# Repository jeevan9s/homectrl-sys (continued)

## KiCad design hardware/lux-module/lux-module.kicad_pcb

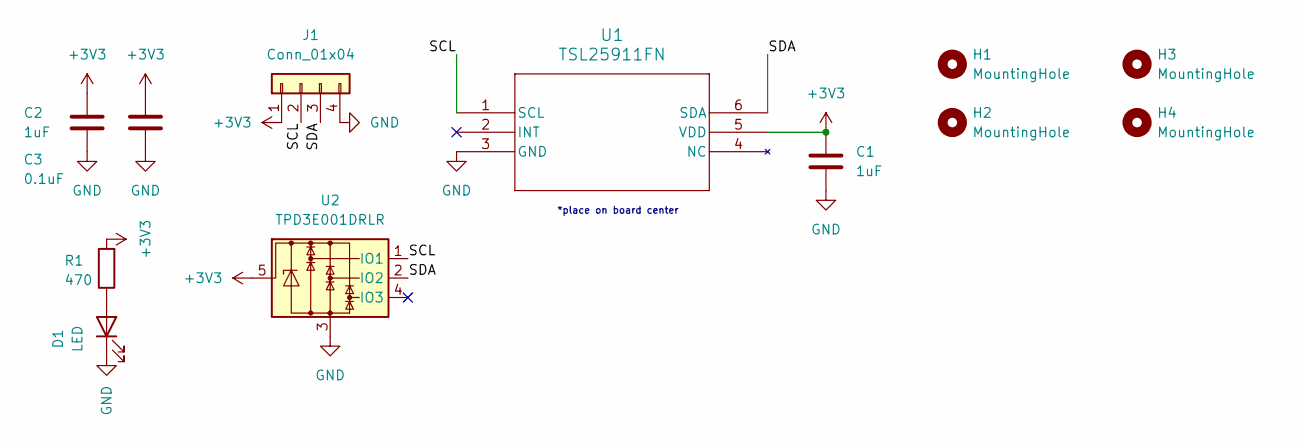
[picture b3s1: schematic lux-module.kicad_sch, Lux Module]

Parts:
C1: 1uF; C_0805_2012Metric; MPN C0805C104K5RACTU
C2: 1uF; C_0805_2012Metric; MPN CL21B106KOQNNNE
C3: 0.1uF; C_0805_2012Metric; MPN CL21B104KBCNNNC
D1: LED; LED_0603_1608Metric
H1, H2, H3, H4: MountingHole; MountingHole_2.2mm_M2; MPN N/A
J1: Conn_01x04; CONN4_S04B-PASK_JST; MPN S04B-PASK-2
R1: 470; R_0402_1005Metric
U1: TSL25911FN; lux-TSL2591; MPN TSL25911FN
U2: TPD3E001DRLR; SOT-553; MPN TPD3E001DRLR

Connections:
+3V3: C1.1, C2.1, C3.1, J1.1, R1.2, U1.5 (VDD), U2.5
/SCL: J1.2, U1.1 (SCL), U2.1 (IO1)
/SDA: J1.3, U1.6 (SDA), U2.2 (IO2)
GND: C1.2, C2.2, C3.2, D1.1 (K), J1.4, U1.3 (GND), U2.3
unnamed: D1.2 (A), R1.1

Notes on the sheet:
*place on board center

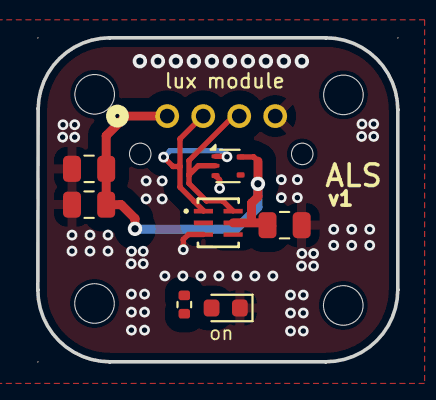
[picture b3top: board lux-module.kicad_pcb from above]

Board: 2 copper layers, 20.0 x 18.0 mm, 12 parts (1 on the bottom side), 5 nets.

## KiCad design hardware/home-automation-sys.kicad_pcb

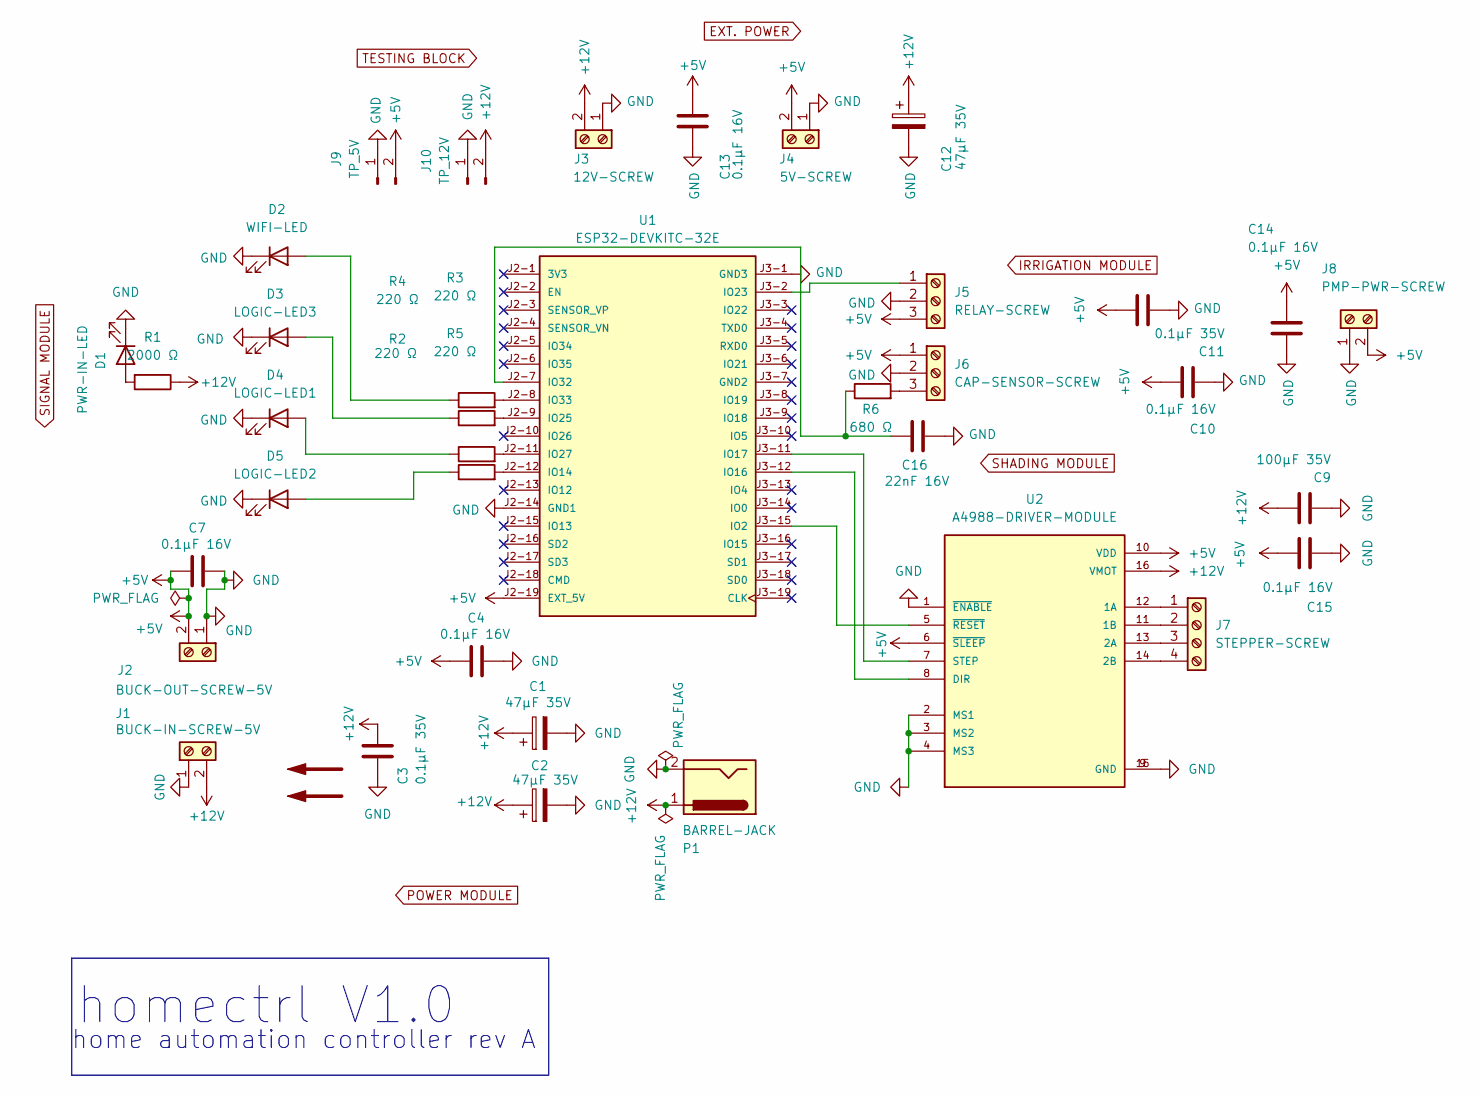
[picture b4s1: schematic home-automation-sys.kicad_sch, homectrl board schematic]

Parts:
C1, C2, C12: 47µF 35V; CP_Radial_D5.0mm_P2.50mm; MPN ECA-1VM470I
C3, C11: 0.1µF 35V; C_0402_1005Metric; MPN GMK105BJ104KV-F
C4: 0.1µF 16V; C_0402_1005Metric; MPN EMK105BJ223KV-F
C7, C10, C13, C14, C15: 0.1µF 16V; C_0402_1005Metric; MPN EMK105BJ104KV-F
C9: 100µF 35V; CP_Radial_D5.0mm_P2.50mm; MPN ECA-1VM101
C16: 22nF 16V; C_0402_1005Metric; MPN EMK105BJ223KV-F
D1: PWR-IN-LED; LED_0402_1005Metric; MPN IN-S42BT5G
D2: WIFI-LED; LED_1206_3216Metric; MPN LTST-C150TBKT
D3: LOGIC-LED3; LED_0805_2012Metric; MPN XZFRS54FVF-1
D4: LOGIC-LED1; LED_0805_2012Metric; MPN 17-21SYGC/S530-E3/TR8
D5: LOGIC-LED2; LED_1206_3216Metric; MPN IN-S85ATA
J1: BUCK-IN-SCREW-5V; TerminalBlock_Phoenix_MKDS-1,5-2_1x02_P5.00mm_Horizontal; MPN 1989447
J2: BUCK-OUT-SCREW-5V; TerminalBlock_Phoenix_MKDS-1,5-2_1x02_P5.00mm_Horizontal; MPN 1989447
J3: 12V-SCREW; TerminalBlock_Phoenix_MKDS-1,5-2_1x02_P5.00mm_Horizontal; MPN 1989447
J4: 5V-SCREW; TerminalBlock_Phoenix_MKDS-1,5-2_1x02_P5.00mm_Horizontal; MPN 1989447
J5: RELAY-SCREW; TerminalBlock_Phoenix_MKDS-1,5-3_1x03_P5.00mm_Horizontal; MPN 1985878
J6: CAP-SENSOR-SCREW; TerminalBlock_Phoenix_MKDS-1,5-3_1x03_P5.00mm_Horizontal; MPN 1985878
J7: STEPPER-SCREW; TerminalBlock_Phoenix_MKDS-1,5-4-5.08_1x04_P5.08mm_Horizont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; MPN 1985878
J8: PMP-PWR-SCREW; TerminalBlock_Phoenix_MKDS-1,5-2_1x02_P5.00mm_Horizontal; MPN 1932410
J9: TP_5V; PinHeader_1x02_P1.00mm_Vertical; MPN TSW-102-07-G-S
J10: TP_12V; PinHeader_1x02_P1.00mm_Vertical; MPN TSW-102-07-G-S
P1: BARREL-JACK; BarrelJack_Horizontal; MPN 54-00134
R1: 2000 Ω; R_0805_2012Metric; MPN ERJ-6ENF2001V
R2, R3, R4, R5: 220 Ω; R_0402_1005Metric; MPN ERA-2AED221X
R6: 680 Ω; R_0402_1005Metric; MPN ERJ-2RKF6800X
U1: ESP32-DEVKITC-32E; MODULE_ESP32-DEVKITC-32D; PARTREV V4
U2: A4988-DRIVER-MODULE; MODULE_A4988_STEPPER_MOTOR_DRIVER_CARRIER; MPN 2986

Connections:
+5V: C4.1, C7.1, C10.1, C11.1, C13.1, C14.1, C15.1, J2.2, J4.2, J5.3, J6.1, J8.2, J9.2, U1.J2-19 (EXT_5V), U2.6 (~SLEEP), U2.10 (VDD)
+12V: C1.1, C2.1, C3.1, C9.1, C12.1, J1.2, J3.2, J10.2, P1.1, R1.1, U2.16 (VMOT)
GND: C1.2, C2.2, C3.2, C4.2, C7.2, C9.2, C10.2, C11.2, C12.2, C13.2, C14.2, C15.2, C16.2, D1.1 (K), D2.1 (K), D3.1 (K), D4.1 (K), D5.1 (K), J1.1, J2.1, J3.1, J4.1, J5.2, J6.2, J8.1, J9.1, J10.1, P1.2, U1.J2-14 (GND1), U1.J3-1 (GND3), U2.1 (~ENABLE), U2.2 (MS1), U2.3 (MS2), U2.4 (MS3), U2.9 (GND), U2.15 (GND)
unnamed: D1.2 (A), R1.2
unnamed: D2.2 (A), R2.1
unnamed: D3.2 (A), R3.1
unnamed: D4.2 (A), R4.1
unnamed: D5.2 (A), R5.1
unnamed: J5.1, U1.J3-2 (IO23)
unnamed: J6.3, R6.2
unnamed: J7.1, U2.12 (1A)
unnamed: J7.2, U2.11 (1B)
unnamed: J7.3, U2.13 (2A)
unnamed: J7.4, U2.14 (2B)
unnamed: U1.J3-15 (IO2), U2.5 (~RESET)
unnamed: R5.2, U1.J2-12 (IO14)
unnamed: U1.J3-12 (IO16), U2.8 (DIR)
unnamed: U1.J3-11 (IO17), U2.7 (STEP)
unnamed: R3.2, U1.J2-9 (IO25)
unnamed: R4.2, U1.J2-11 (IO27)
unnamed: C16.1, R6.1, U1.J2-7 (IO32)
unnamed: R2.2, U1.J2-8 (IO33)

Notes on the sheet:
homectrl V1.0
home automation controller rev A

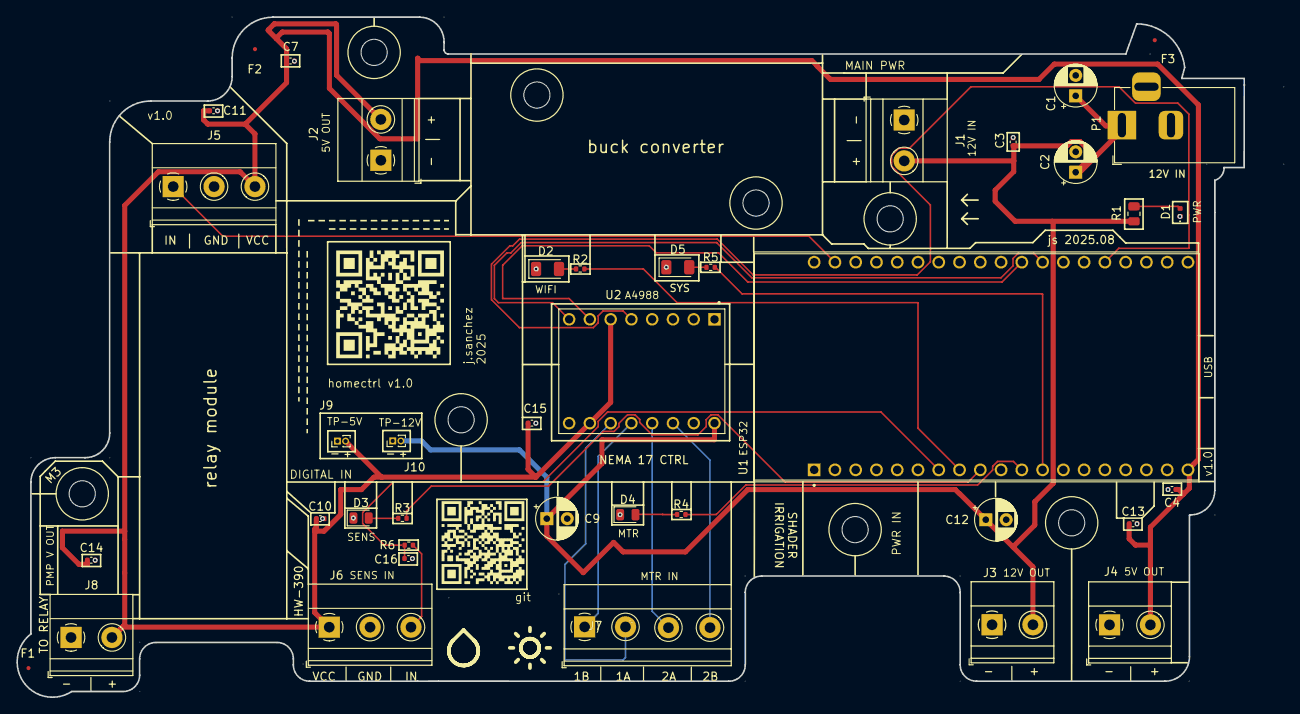
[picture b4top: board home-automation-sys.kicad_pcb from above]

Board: 2 copper layers, 154.9 x 83.2 mm, 37 parts (0 on the bottom side), 22 nets.

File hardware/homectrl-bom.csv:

"Value","Reference","Footprint","Qty","MPN"
"47µF 35V","C1,C2,C12","Capacitor_THT:CP_Radial_D5.0mm_P2.50mm","3","ECA-1VM470I"
"0.1µF 35V","C3,C11","Capacitor_SMD:C_0402_1005Metric","2","GMK105BJ104KV-F"
"0.1µF 16V","C4,C7,C10,C13,C14,C15","Capacitor_SMD:C_0402_1005Metric","6","-- mixed values --"
"100µF 35V","C9","Capacitor_THT:CP_Radial_D5.0mm_P2.50mm","1","ECA-1VM101"
"22nF 16V","C16","Capacitor_SMD:C_0402_1005Metric","1","  EMK105BJ223KV-F"
"PWR-IN-LED","D1","LED_SMD:LED_0402_1005Metric","1","IN-S42BT5G"
"WIFI-LED","D2","LED_SMD:LED_1206_3216Metric","1","LTST-C150TBKT"
"LOGIC-LED3","D3","LED_SMD:LED_0805_2012Metric","1","XZFRS54FVF-1"
"LOGIC-LED1","D4","LED_SMD:LED_0805_2012Metric","1","17-21SYGC/S530-E3/TR8"
"LOGIC-LED2","D5","LED_SMD:LED_1206_3216Metric","1","IN-S85ATA"
"BUCK-IN-SCREW-5V","J1","TerminalBlock_Phoenix:TerminalBlock_Phoenix_MKDS-1,5-2_1x02_P5.00mm_Horizontal","1","  1989447"
"BUCK-OUT-SCREW-5V","J2","TerminalBlock_Phoenix:TerminalBlock_Phoenix_MKDS-1,5-2_1x02_P5.00mm_Horizontal","1","  1989447"
"12V-SCREW","J3","TerminalBlock_Phoenix:TerminalBlock_Phoenix_MKDS-1,5-2_1x02_P5.00mm_Horizontal","1","  1989447"
"5V-SCREW","J4","TerminalBlock_Phoenix:TerminalBlock_Phoenix_MKDS-1,5-2_1x02_P5.00mm_Horizontal","1","  1989447"
"RELAY-SCREW","J5","TerminalBlock_Phoenix:TerminalBlock_Phoenix_MKDS-1,5-3_1x03_P5.00mm_Horizontal","1","1985878"
"CAP-SENSOR-SCREW","J6","TerminalBlock_Phoenix:TerminalBlock_Phoenix_MKDS-1,5-3_1x03_P5.00mm_Horizontal","1","1985878"
"STEPPER-SCREW","J7","TerminalBlock_Phoenix:TerminalBlock_Phoenix_MKDS-1,5-4-5.08_1x04_P5.08mm_Horizontal","1","1985878"
"PMP-PWR-SCREW","J8","TerminalBlock_Phoenix:TerminalBlock_Phoenix_MKDS-1,5-2_1x02_P5.00mm_Horizontal","1","1932410"
"TP_5V","J9","Connector_PinHeader_1.00mm:PinHeader_1x02_P1.00mm_Vertical","1","TSW-102-07-G-S"
"TP_12V","J10","Connector_PinHeader_1.00mm:PinHeader_1x02_P1.00mm_Vertical","1","TSW-102-07-G-S"
"BARREL-JACK","P1","Connector_BarrelJack:BarrelJack_Horizontal","1","54-00134"
"2000 Ω","R1","Resistor_SMD:R_0805_2012Metric","1","ERJ-6ENF2001V"
"220 Ω","R2,R3,R4,R5","Resistor_SMD:R_0402_1005Metric","4","ERA-2AED221X"
"680 Ω","R6","Resistor_SMD:R_0402_1005Metric","1","ERJ-2RKF6800X"
"ESP32-DEVKITC-32E","U1","ESP32-DEVKITC-32D:MODULE_ESP32-DEVKITC-32D","1","ESP32-DevKitC-32E"
"A4988-DRIVER-MODULE","U2","A4988_STEPPER_MOTOR_DRIVER_CARRIER:MODULE_A4988_STEPPER_MOTOR_DRIVER_CARRIER","1","  2986"

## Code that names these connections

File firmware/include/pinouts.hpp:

/**
 * @file        pinouts.hpp
 * @brief       Board pinout definitions
 * @author      Jeevan Sanchez
 * @date        2026-07-18
 *
 * HOMECTRL
 */

#pragma once

#include <cstdint>

namespace Pins
{
    namespace Power
    {
        constexpr uint8_t VSMS_EN = 2;
        constexpr uint8_t VPMP_SENSE = 4;
        constexpr uint8_t VPMP_EN = 16;
    }

    namespace Actuators
    {
        constexpr uint8_t PUMP1_EN = 7;
        constexpr uint8_t PUMP0_EN = 15;
        constexpr uint8_t TMC_DIAG = 9;
        constexpr uint8_t TMC_ENN = 10;
        constexpr uint8_t TMC_STEP = 17;
        constexpr uint8_t TMC_DIR = 18;
    }

    namespace Data
    {
        constexpr uint8_t SMS0_ADATA = 5;
        constexpr uint8_t SMS1_ADATA = 6;
        constexpr uint8_t FSW1_SIG = 41;
        constexpr uint8_t FSW2_SIG = 42;
    }

    namespace Indicators
    {
        constexpr uint8_t RGB_LED = 11;
        constexpr uint8_t WIFI_LED = 12;
        constexpr uint8_t DBG_LED = 13;
        constexpr uint8_t BUZZ_EN = 47;

    }

    constexpr uint8_t S3_TXD = 3;

    constexpr uint8_t S3_RXD = 8;

    constexpr uint8_t I2C_SCL = 14;

    constexpr uint8_t I2C_SDA = 21;

}

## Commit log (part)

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2025-07-27 Create test
2025-07-27 add system workflow
2025-07-27 add sys workflow
2025-07-27 add shading workflow
2025-07-30 Create s
2025-07-30 add schematic diagram
2025-07-30 add schematic v1
2025-07-30 add schematic v2
2025-07-30 add pro file for laptop workspace
2025-07-30 v2 add for laptop workspace
2025-07-31 add schematic v3
2025-08-10 web-app init
2025-08-11 add schematic v4
2025-08-11 add v4 schematic
2025-08-13 ui changes
2025-08-16 page web app work
2025-08-16 done (before fetches)
2025-08-17 app backend, arduino dir init
2025-08-20 updates to software-side
2025-08-21 irrigation header
2025-08-22 software side work
2025-08-22 irrigation module
2025-08-22 irrigation module + sinric
2025-08-22 shading module done
2025-08-22 main
2025-08-29 add schematic v5
2025-08-29 add gerbers and pos
    ignore BOM here
2025-10-03 repo refactor
2025-10-03 add img
2025-10-03 add power image
2025-10-03 Update README.md
    update README
2025-11-23 implement testing
2025-12-23 lux module schematic
2025-12-24 setup schematic hiearchy
2025-12-29 finish lux moudle/ALS
2025-12-29 power circuitry
2025-12-29 assign footprints
2025-12-30 pmux & breakout circuitry
2025-12-30 sensing circuitry
2025-12-31 stepper driver circuitry
2026-01-03 layout work
2026-01-04 routing work
2026-01-05 more routing work
2026-01-06 more more routing routing work work
2026-01-07 silkscreen, review work
2026-01-07 switch commit
2026-01-07 back silkscreen
2026-01-07 fix some text stuff
2026-01-07 getting there
2026-01-08 add new caps, add ferrite bead, add MPNs
2026-01-10 add MPNs and review circuits
2026-01-10 same
2026-01-11 review, add vias & ground pour
2026-01-11 finalizing changes
2026-01-13 pad clearance & BOM fixes
2026-01-16 swap connector in progress
2026-01-16 changes for connector revision
2026-01-17 connector fixes
2026-01-17 more conn changes
2026-01-20 add AGND, more layout work
2026-01-21 dssadasdas
2026-01-22 BOM fix
2026-02-04 repo-organization
2026-02-05 silkscreen chantges
2026-02-09 work
2026-02-09 merge
2026-02-09 remove py
2026-02-09 b.si
2026-02-11 update ALS
2026-02-11 readme updates
2026-02-24 test fw work
2026-02-27 write testing firmware
2026-03-17 Add .gitattributes to ignore HTML files in linguist
2026-05-31 firmware design refactor
2026-06-11 init r2
2026-06-12 added pinouts
2026-06-12 sch work
2026-06-13 entry circuits
2026-06-14 peirpheral circuit work
2026-06-14 tmc2209 wiring
2026-06-14 power calculations
2026-06-15 power layout
2026-06-15 fet fix
2026-06-15 experimenting w connectors
2026-06-15 connectot placement
2026-06-16 power routing
2026-06-16 actuator routes
2026-06-17 misc work
2026-06-17 start signal routes
2026-06-17 dasdf
2026-06-17 more signal routing
2026-06-17 finish component routing
2026-06-17 logic power routing
2026-06-18 board outline done
2026-06-19 reroute esp pins
2026-06-19 wrapping up layout & routing
2026-06-19 reviewed
2026-06-19 added part numbers
2026-06-20 start silkscreen
2026-06-20 silkscreen
2026-06-20 prod
2026-06-22 prods
2026-06-22 add models
2026-06-28 cleanup
2026-06-28 readme organization
2026-06-28 add controller imgs
2026-06-28 widths
2026-06-28 more width changes
2026-06-28 another width change
2026-06-28 overview
2026-06-28 feature docs
2026-06-28 add imgs
2026-06-30 pump drivers
2026-06-30 update img title
2026-06-30 finish hardware docs
2026-06-30 center imgs
